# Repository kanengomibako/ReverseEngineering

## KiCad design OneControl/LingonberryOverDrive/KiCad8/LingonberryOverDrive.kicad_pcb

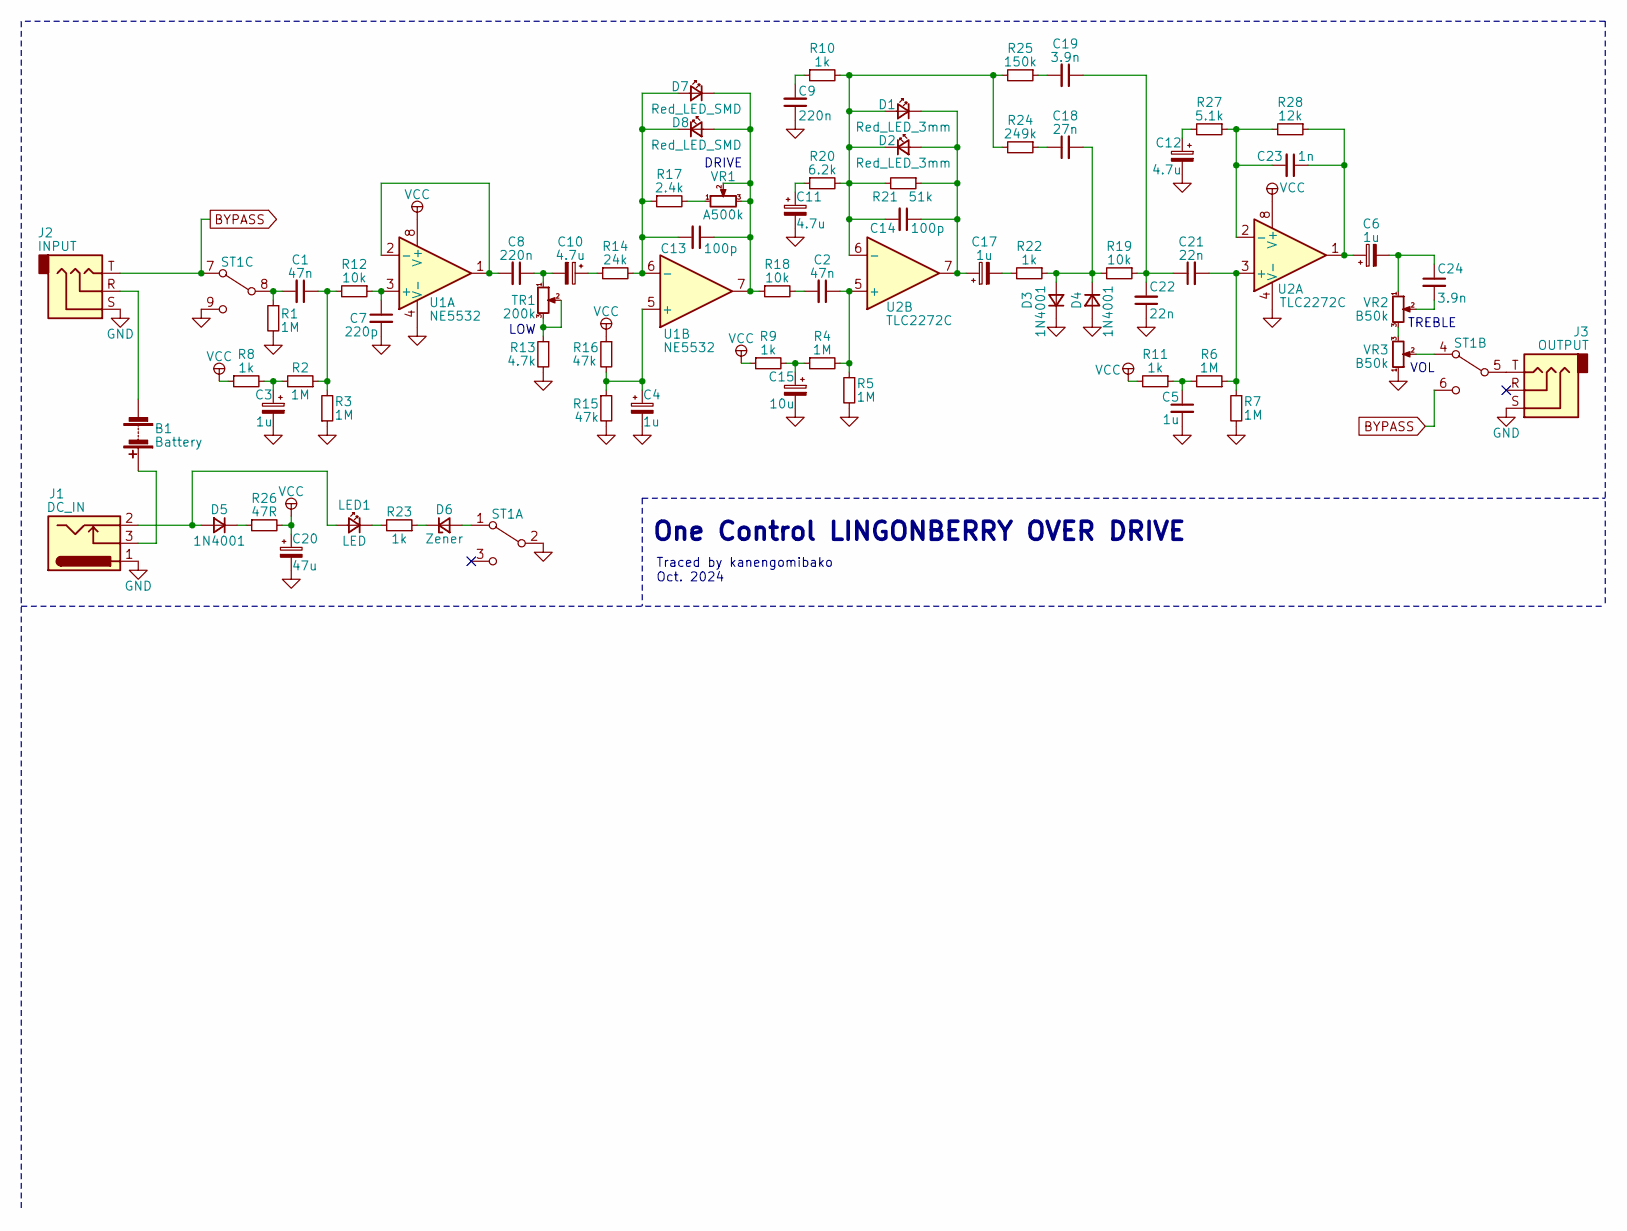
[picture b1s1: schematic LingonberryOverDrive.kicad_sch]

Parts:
B1: Battery; my_conn
C1, C2: 47n; C_Rect_L7.0mm_W2.0mm_P5.00mm
C3, C4, C6, C17: 1u; CP_Elec_4x5.4
C5: 1u; C_0805_2012Metric
C7: 220p; C_0603_1608Metric
C8, C9: 220n; C_Rect_L7.0mm_W2.0mm_P5.00mm
C10, C11, C12: 4.7u; CP_Elec_4x5.4
C13, C14: 100p; C_0603_1608Metric
C15: 10u; CP_Elec_4x5.4
C18: 27n; C_Rect_L7.0mm_W2.0mm_P5.00mm
C19, C24: 3.9n; C_Rect_L7.0mm_W2.0mm_P5.00mm
C20: 47u; CP_Elec_5x5.4
C21, C22: 22n; C_Rect_L7.0mm_W2.0mm_P5.00mm
C23: 1n; C_0603_1608Metric
D1, D2: Red_LED_3mm; my_LED_3mm
D3, D4, D5: 1N4001; D_SOD-128
D6: Zener; D_SOD-123
D7, D8: Red_LED_SMD; D_0603_1608Metric
J1: DC_IN; my_DC_Jack
J2: INPUT; PJ-603A
J3: OUTPUT; PJ-603A
LED1: LED; my_LED_5mm
R1, R2, R3, R4, R5, R6, R7: 1M; R_0603_1608Metric
R8, R9, R10, R11, R22, R23: 1k; R_0603_1608Metric
R12, R18, R19: 10k; R_0603_1608Metric
R13: 4.7k; R_0603_1608Metric
R14: 24k; R_0603_1608Metric
R15, R16: 47k; R_0603_1608Metric
R17: 2.4k; R_0603_1608Metric
R20: 6.2k; R_0603_1608Metric
R21: 51k; R_0603_1608Metric
R24: 249k; R_0603_1608Metric
R25: 150k; R_0603_1608Metric
R26: 47R; R_0603_1608Metric
R27: 5.1k; R_0603_1608Metric
R28: 12k; R_0603_1608Metric
ST1: SW; my_sw_3pdt_fujisoku
TR1: 200k; my_trim2
U1: NE5532; SOP-8_3.9x4.9mm_P1.27mm
U2: TLC2272C; SOP-8_3.9x4.9mm_P1.27mm
VR1: A500k; PinHeader_1x03_P2.54mm_Vertical
VR2, VR3: B50k; PinHeader_1x03_P2.54mm_Vertical

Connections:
BYPASS: J2.T, ST1.6 (C), ST1.7 (A)
GND: C3.2, C4.2, C5.2, C7.2, C9.1, C11.2, C12.2, C15.2, C20.2, C22.1, D3.1 (K), D4.2 (A), J1.1, J2.S, J3.S, R1.2, R3.1, R5.2, R7.2, R13.2, R15.2, ST1.2 (B), ST1.9 (C), U1.4 (V-), U2.4 (V-), VR3.1
unnamed: B1.1 (+), J1.3
unnamed: B1.2 (-), J2.R
unnamed: C1.1, R2.1, R3.2, R12.2
unnamed: C2.2, R18.2
unnamed: C3.1, R2.2, R8.2
unnamed: C5.1, R6.2, R11.1
unnamed: C9.2, R10.1
unnamed: C10.1, R14.1
unnamed: C8.1, C10.2, TR1.1
unnamed: C11.1, R20.1
unnamed: C12.1, R27.2
unnamed: C15.1, R4.1, R9.2
unnamed: C17.2, R22.2
unnamed: C18.1, R24.1
unnamed: C19.1, C21.1, C22.2, R19.1
unnamed: C19.2, R25.1
unnamed: C6.1, C23.1, R28.1, U2.1
unnamed: C6.2, C24.1, VR2.1
unnamed: C24.2, VR2.2
unnamed: C14.2, D1.2 (A), D2.1 (K), R10.2, R20.2, R21.2, R24.2, R25.2, U2.6 (-)
unnamed: C14.1, C17.1, D1.1 (K), D2.2 (A), R21.1, U2.7
unnamed: C18.2, D3.2 (A), D4.1 (K), R19.2, R22.1
unnamed: D5.2 (A), J1.2, LED1.2 (A)
unnamed: D5.1 (K), R26.1
unnamed: D6.2 (A), ST1.1 (A)
unnamed: D6.1 (K), R23.1
unnamed: C13.2, D7.2 (A), D8.1 (K), R14.2, R17.1, U1.6 (-)
unnamed: C13.1, D7.1 (K), D8.2 (A), R18.1, U1.7, VR1.2, VR1.3
unnamed: LED1.1 (K), R23.2
unnamed: R13.1, TR1.2, TR1.3
unnamed: R17.2, VR1.1
unnamed: ST1.4 (A), VR3.2
unnamed: J3.T, ST1.5 (B)
unnamed: C1.2, R1.1, ST1.8 (B)
unnamed: C7.1, R12.1, U1.3 (+)
unnamed: C8.2, U1.1, U1.2 (-)
unnamed: C4.1, R15.1, R16.2, U1.5 (+)
unnamed: C21.2, R6.1, R7.1, U2.3 (+)
unnamed: C23.2, R27.1, R28.2, U2.2 (-)
unnamed: C2.1, R4.2, R5.1, U2.5 (+)
unnamed: VR2.3, VR3.3
VCC: C20.1, R8.1, R9.1, R11.2, R16.1, R26.2, U1.8 (V+), U2.8 (V+)

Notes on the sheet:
TREBLE
One Control LINGONBERRY OVER DRIVE
LOW
Traced by kanengomibako Oct. 2024
DRIVE
VOL

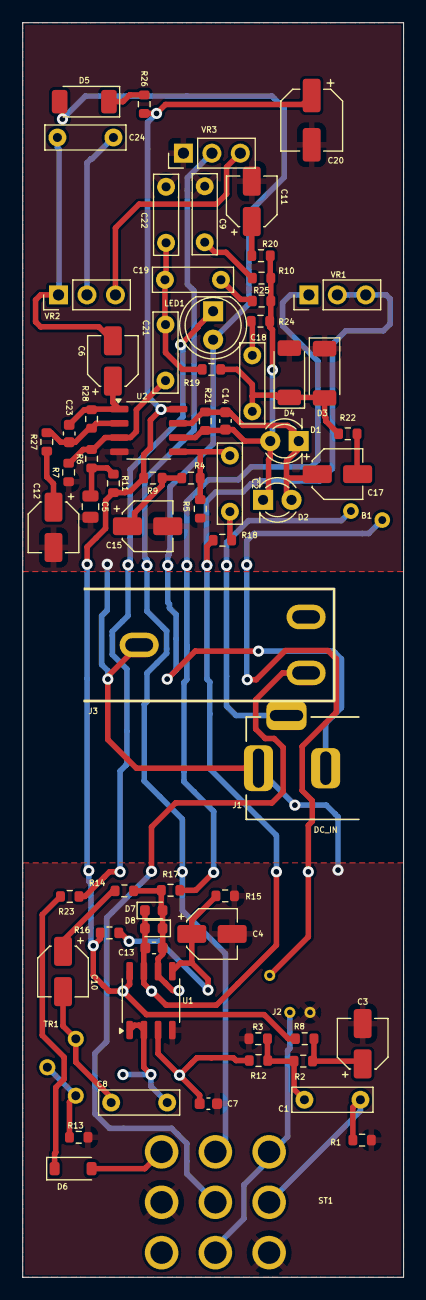
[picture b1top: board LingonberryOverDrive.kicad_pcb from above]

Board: 2 copper layers, 34.0 x 112.0 mm, 71 parts (0 on the bottom side), 44 nets.

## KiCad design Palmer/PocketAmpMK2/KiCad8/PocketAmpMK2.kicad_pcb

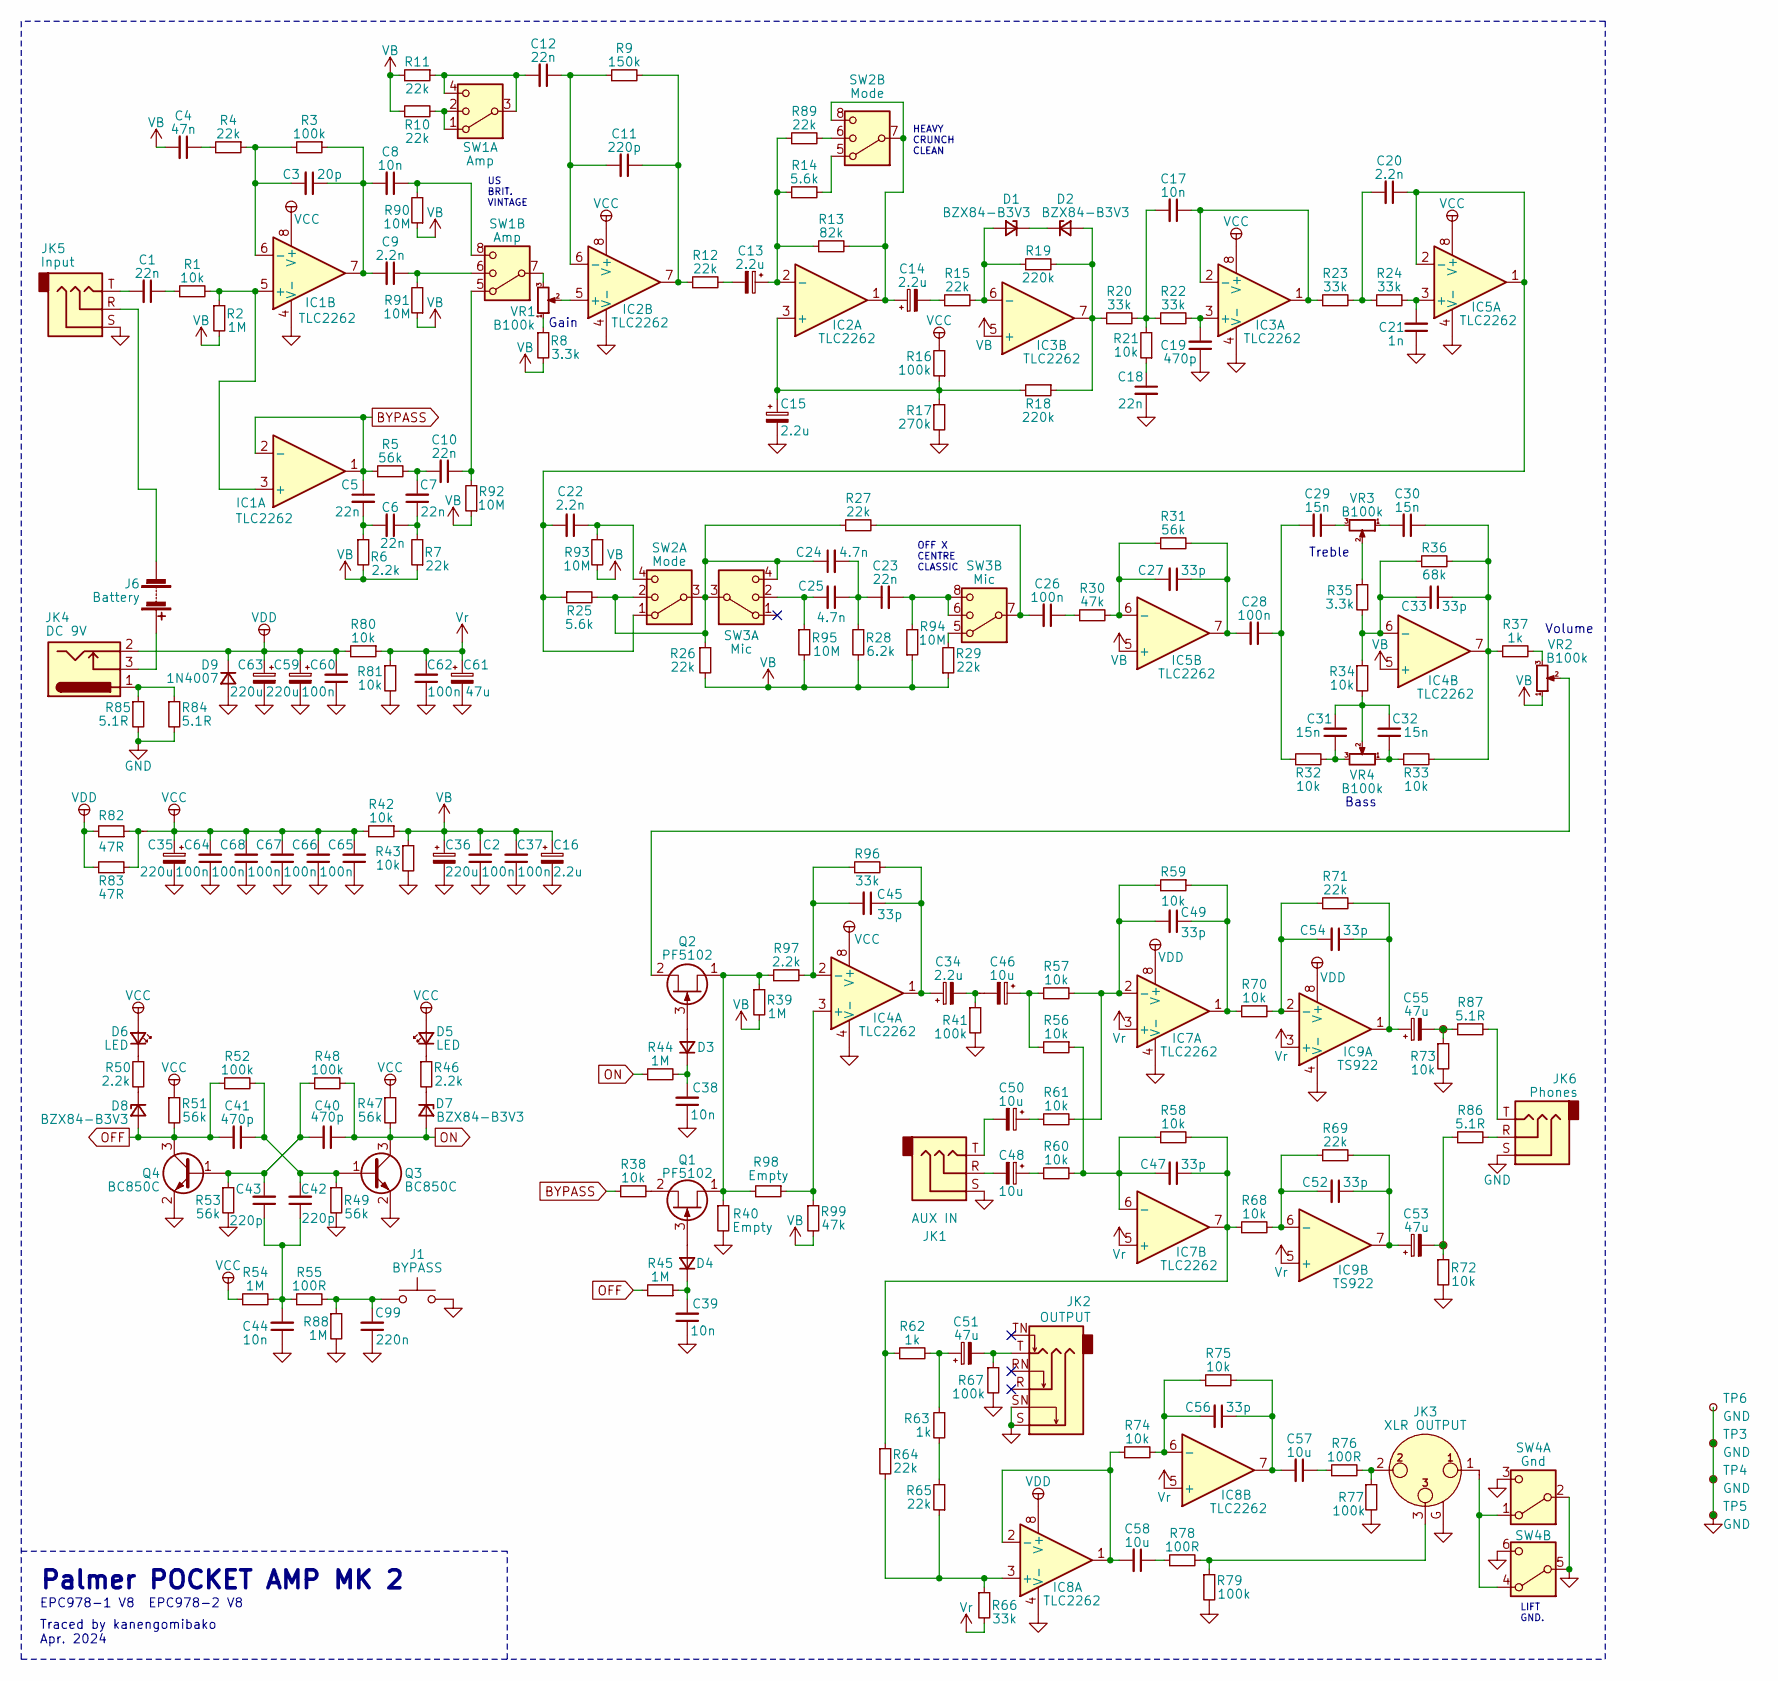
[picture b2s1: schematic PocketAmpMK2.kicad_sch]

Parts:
C1: 22n; C_Rect_L7.0mm_W2.0mm_P5.00mm
C2, C26, C28, C37, C60, C62, C64, C65, C66, C67, C68: 100n; RC_0805_2012Metric_mxr
C3: 20p; RC_0805_2012Metric_mxr
C4: 47n; RC_0805_2012Metric_mxr
C5, C6, C7, C10, C12, C18, C23: 22n; RC_0805_2012Metric_mxr
C8, C17, C38, C39, C44: 10n; RC_0805_2012Metric_mxr
C9, C20, C22: 2.2n; RC_0805_2012Metric_mxr
C11, C42, C43: 220p; RC_0805_2012Metric_mxr
C13, C14, C15, C16, C34: 2.2u; CP_Radial_D4.0mm_P2.00mm
C19, C40, C41: 470p; RC_0805_2012Metric_mxr
C21: 1n; RC_0805_2012Metric_mxr
C24, C25: 4.7n; RC_0805_2012Metric_mxr
C27, C33, C45, C47, C49, C52, C54, C56: 33p; RC_0805_2012Metric_mxr
C29, C30, C31, C32: 15n; RC_0805_2012Metric_mxr
C35, C36, C59, C63: 220u; CP_Radial_D6.3mm_P2.50mm
C46, C48, C50: 10u; CP_Radial_D4.0mm_P2.00mm
C51, C53, C55, C61: 47u; CP_Radial_D4.0mm_P2.00mm
C57, C58: 10u; C_Disc_D3.8mm_W2.6mm_P2.50mm
C99: 220n; RC_0805_2012Metric_mxr
CN1: out; my_conn
CN2: vcc; my_conn
CN3: xlr; my_conn
D1, D2, D7, D8: BZX84-B3V3; SOT-23
D3, D4: ?; D_MiniMELF
D5, D6: LED; LED_D3.0mm
D9: 1N4007; D_DO-35_SOD27_P10.16mm_Horizontal
IC1, IC2, IC3, IC4, IC5, IC7, IC8: TLC2262; SOIC-8_3.9x4.9mm_P1.27mm
IC9: TS922; SOIC-8_3.9x4.9mm_P1.27mm
J1: BYPASS; my_conn
J6: Battery; my_conn
JK1: AUX IN; PinHeader_1x03_P2.54mm_Vertical
JK2: OUTPUT; Jack_6.35mm_Neutrik_NMJ6HCD3_Horizontal
JK3: XLR OUTPUT; Jack_XLR_Neutrik_NC3MAAH-0_Horizontal
JK4: DC 9V; my_DC_Jack
JK5: Input; PinHeader_1x03_P2.54mm_Vertical
JK6: Phones; PinHeader_1x03_P2.54mm_Vertical
Q1, Q2: PF5102; TO-92_Inline_Wide
Q3, Q4: BC850C; SOT-23
R1, R21, R32, R33, R34, R38, R42, R43, R56, R57, R58, R59, R60, R61, R68, R70, R72, R73, R74, R75, R80, R81: 10k; RC_0805_2012Metric_mxr
R2, R39, R44, R45, R54, R88: 1M; RC_0805_2012Metric_mxr
R3, R16, R41, R48, R52, R67, R77, R79: 100k; RC_0805_2012Metric_mxr
R4, R7, R10, R11, R12, R15, R26, R27, R29, R64, R65, R69, R71, R89: 22k; RC_0805_2012Metric_mxr
R5, R31, R47, R49, R51, R53: 56k; RC_0805_2012Metric_mxr
R6, R46, R50, R97: 2.2k; RC_0805_2012Metric_mxr
R8, R35: 3.3k; RC_0805_2012Metric_mxr
R9: 150k; RC_0805_2012Metric_mxr
R13: 82k; RC_0805_2012Metric_mxr
R14, R25: 5.6k; RC_0805_2012Metric_mxr
R17: 270k; RC_0805_2012Metric_mxr
R18, R19: 220k; RC_0805_2012Metric_mxr
R20, R22, R23, R24, R66, R96: 33k; RC_0805_2012Metric_mxr
R28: 6.2k; RC_0805_2012Metric_mxr
R30, R99: 47k; RC_0805_2012Metric_mxr
R36: 68k; RC_0805_2012Metric_mxr
R37, R62, R63: 1k; RC_0805_2012Metric_mxr
R40, R98: Empty; RC_0805_2012Metric_mxr
R55, R76, R78: 100R; RC_0805_2012Metric_mxr
R82, R83: 47R; RC_0805_2012Metric_mxr
R84, R85: 5.1R; RC_0805_2012Metric_mxr
R86, R87: 5.1R; R_Axial_DIN0207_L6.3mm_D2.5mm_P10.16mm_Horizontal
R90, R91, R92, R93, R94, R95: 10M; RC_0805_2012Metric_mxr
SW1: Amp; PinHeader_2x04_P2.54mm_Vertical
SW2: Mode; PinHeader_2x04_P2.54mm_Vertical
SW3: Mic; PinHeader_2x04_P2.54mm_Vertical
SW4: Gnd; SW_CK_JS202011CQN_DPDT_Straight
TP1: out1; my_SmallestPad_0-72mmDrill
TP2: out2; my_SmallestPad_0-72mmDrill
TP3, TP4, TP5, TP6: GND; my_SmallestPad_0-72mmDrill
VR1, VR2, VR3, VR4: B100k; PinHeader_1x03_P2.54mm_Vertical

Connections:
BYPASS: C5.1, IC1.1, IC1.2 (-), R5.1, R38.1
GND: C2.1, C15.2, C16.2, C18.2, C19.1, C21.1, C35.2, C36.2, C37.1, C38.1, C39.1, C44.1, C59.2, C60.1, C61.2, C62.1, C63.2, C64.1, C65.1, C66.1, C67.1, C68.1, C99.1, D9.2 (A), IC1.4 (V-), IC2.4 (V-), IC3.4 (V-), IC4.4 (V-), IC5.4 (V-), IC7.4 (V-), IC8.4 (V-), IC9.4 (V-), J1.1, JK1.S, JK2.S, JK2.SN, JK3.G, JK5.S, JK6.S, Q3.2 (E), Q4.2 (E), R17.2, R40.2, R41.2, R43.2, R49.2, R53.2, R67.2, R72.2, R73.2, R77.2, R79.2, R81.2, R84.2, R85.2, R88.2, SW4.2 (B), SW4.3 (C), SW4.5 (B), SW4.6 (C), TP3.1, TP4.1, TP5.1, TP6.1
unnamed: C1.1, R1.1
unnamed: C1.2, JK5.T
unnamed: C3.1, C8.2, C9.2, IC1.7, R3.1
unnamed: C4.1, R4.2
unnamed: C5.2, C6.2, R6.1
unnamed: C6.1, C7.1, R7.2
unnamed: C8.1, R90.2, SW1.8
unnamed: C9.1, R91.2, SW1.6
unnamed: C10.1, R92.2, SW1.5
unnamed: C7.2, C10.2, R5.2
unnamed: C11.1, IC2.7, R9.2, R12.1
unnamed: C12.2, R10.1, SW1.3, SW1.4
unnamed: C13.2, R12.2
unnamed: C14.1, IC2.1, R13.2, SW2.7, SW2.8
unnamed: C14.2, R15.1
unnamed: C17.2, R20.2, R21.2, R22.1
unnamed: C18.1, R21.1
unnamed: C20.2, R23.2, R24.1
unnamed: C22.1, R93.1, SW2.4
unnamed: C23.1, C24.2, C25.1, R28.1
unnamed: C23.2, R94.2, SW3.6, SW3.8
unnamed: C24.1, R25.2, R26.1, R27.1, SW2.2, SW2.3, SW3.3, SW3.4
unnamed: C25.2, R95.1, SW3.2
unnamed: C26.1, R30.1
unnamed: C26.2, R27.2, SW3.7
unnamed: C27.1, C28.2, IC5.7, R31.2
unnamed: C28.1, C29.2, R32.1
unnamed: C29.1, VR3.3
unnamed: C30.1, C33.1, IC4.7, R33.2, R36.2, R37.1
unnamed: C30.2, VR3.1
unnamed: C31.1, R32.2, VR4.3
unnamed: C31.2, C32.2, R34.2, VR4.2
unnamed: C32.1, R33.1, VR4.1
unnamed: C34.1, C45.1, IC4.1, R96.2
unnamed: C34.2, CN1.2, R41.1
unnamed: C42.1, C43.1, C44.2, R54.2, R55.1
unnamed: C46.1, R56.2, R57.1
unnamed: C46.2, CN1.1
unnamed: C47.1, IC7.7, R58.2, R62.1, R64.1, R68.1
unnamed: C48.1, R60.1
unnamed: C48.2, JK1.R
unnamed: C49.1, IC7.1, R59.1, R70.1
unnamed: C50.1, R61.1
unnamed: C50.2, JK1.T
unnamed: C51.1, R62.2, R63.1
unnamed: C51.2, JK2.T, R67.1
unnamed: C52.1, C53.1, IC9.7, R69.2
unnamed: C53.2, R72.1, R86.1, TP2.1
unnamed: C54.1, C55.1, IC9.1, R71.2
unnamed: C55.2, R73.1, R87.1, TP1.1
unnamed: C56.1, C57.2, IC8.7, R75.2
unnamed: C57.1, R76.1
unnamed: C58.1, R78.1
unnamed: CN2.1, R82.1, R83.1
unnamed: CN3.1, JK3.1
unnamed: D1.1 (A), IC3.6 (-), R15.2, R19.1
unnamed: D1.3 (K), D2.3 (K)
unnamed: D2.1 (A), IC3.7, R18.1, R19.2, R20.1
unnamed: D3.2 (A), Q2.3 (G)
unnamed: C38.2, D3.1 (K), R44.2
unnamed: D4.2 (A), Q1.3 (G)
unnamed: C39.2, D4.1 (K), R45.1
unnamed: D5.1 (K), R46.1
unnamed: D6.1 (K), R50.1
unnamed: D7.3 (K), R46.2
unnamed: D8.3 (K), R50.2
unnamed: IC1.3 (+), IC1.5 (+), R1.2, R2.1
unnamed: C3.2, IC1.6 (-), R3.2, R4.1
unnamed: C15.1, IC2.3 (+), R16.1, R17.1, R18.2
unnamed: C13.1, IC2.2 (-), R13.1, R14.1, R89.1
unnamed: IC2.5 (+), VR1.2
unnamed: C11.2, C12.1, IC2.6 (-), R9.1
unnamed: C19.2, IC3.3 (+), R22.2
unnamed: C17.1, IC3.1, IC3.2 (-), R23.1
unnamed: IC4.3 (+), R98.1, R99.1
unnamed: C45.2, IC4.2 (-), R96.1, R97.2
unnamed: C33.2, IC4.6 (-), R34.1, R35.2, R36.1
unnamed: C21.2, IC5.3 (+), R24.2
unnamed: C20.1, C22.2, IC5.1, IC5.2 (-), R25.1, SW2.1
unnamed: C27.2, IC5.6 (-), R30.2, R31.1
unnamed: C49.2, IC7.2 (-), R57.2, R59.2, R61.2
unnamed: C47.2, IC7.6 (-), R56.1, R58.1, R60.2
unnamed: IC8.3 (+), R64.2, R65.1, R66.1
unnamed: C58.2, IC8.1, IC8.2 (-), R74.1
unnamed: C56.2, IC8.6 (-), R74.2, R75.1
unnamed: C54.2, IC9.2 (-), R70.2, R71.1
unnamed: C52.2, IC9.6 (-), R68.2, R69.1
unnamed: C99.2, J1.2, R55.2, R88.1
unnamed: J6.1 (+), JK4.3
unnamed: J6.2 (-), JK5.R
unnamed: JK3.2, R76.2, R77.1
unnamed: JK3.3, R78.2, R79.1
unnamed: JK4.1, R84.1, R85.1
unnamed: JK6.R, R86.2
unnamed: JK6.T, R87.2
unnamed: Q1.1 (D), Q2.1 (D), R39.1, R40.1, R97.1, R98.2
unnamed: Q1.2 (S), R38.2
unnamed: Q2.2 (S), VR2.2
unnamed: C41.1, C42.2, Q3.1 (B), R49.1, R52.2
unnamed: C40.2, C43.2, Q4.1 (B), R48.1, R53.1
unnamed: R8.1, VR1.1
unnamed: R11.2, SW1.1, SW1.2
unnamed: R14.2, SW2.5
unnamed: R29.2, SW3.5
unnamed: R35.1, VR3.2
unnamed: R37.2, VR2.3
unnamed: R63.2, R65.2
unnamed: R89.2, SW2.6
unnamed: SW1.7, VR1.3
unnamed: CN3.2, SW4.1 (A), SW4.4 (A)
OFF: C41.2, D8.1 (A), Q4.3 (C), R45.2, R51.2, R52.1
ON: C40.1, D7.1 (A), Q3.3 (C), R44.1, R47.2, R48.2
VB: C2.2, C4.2, C16.1, C36.1, C37.2, IC3.5 (+), IC4.5 (+), IC5.5 (+), R2.2, R6.2, R7.1, R8.2, R10.2, R11.1, R26.2, R28.2, R29.1, R39.2, R42.1, R43.1, R90.1, R91.1, R92.1, R93.2, R94.1, R95.2, R99.2, VR2.1
VCC: C35.1, C64.2, C65.2, C66.2, C67.2, C68.2, CN2.2, D5.2 (A), D6.2 (A), IC1.8 (V+), IC2.8 (V+), IC3.8 (V+), IC4.8 (V+), IC5.8 (V+), R16.2, R42.2, R47.1, R51.1, R54.1
VDD: C59.1, C60.2, C63.1, D9.1 (K), IC7.8 (V+), IC8.8 (V+), IC9.8 (V+), JK4.2, R80.2, R82.2, R83.2
Vr: C61.1, C62.2, IC7.3 (+), IC7.5 (+), IC8.5 (+), IC9.3 (+), IC9.5 (+), R66.2, R80.1, R81.1

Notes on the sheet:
Treble
Bass
Palmer POCKET AMP MK 2
EPC978-1 V8 EPC978-2 V8
US BRIT. VINTAGE
LIFT GND.
Volume
Traced by kanengomibako Apr. 2024
HEAVY CRUNCH CLEAN
Gain
OFF X CENTRE CLASSIC

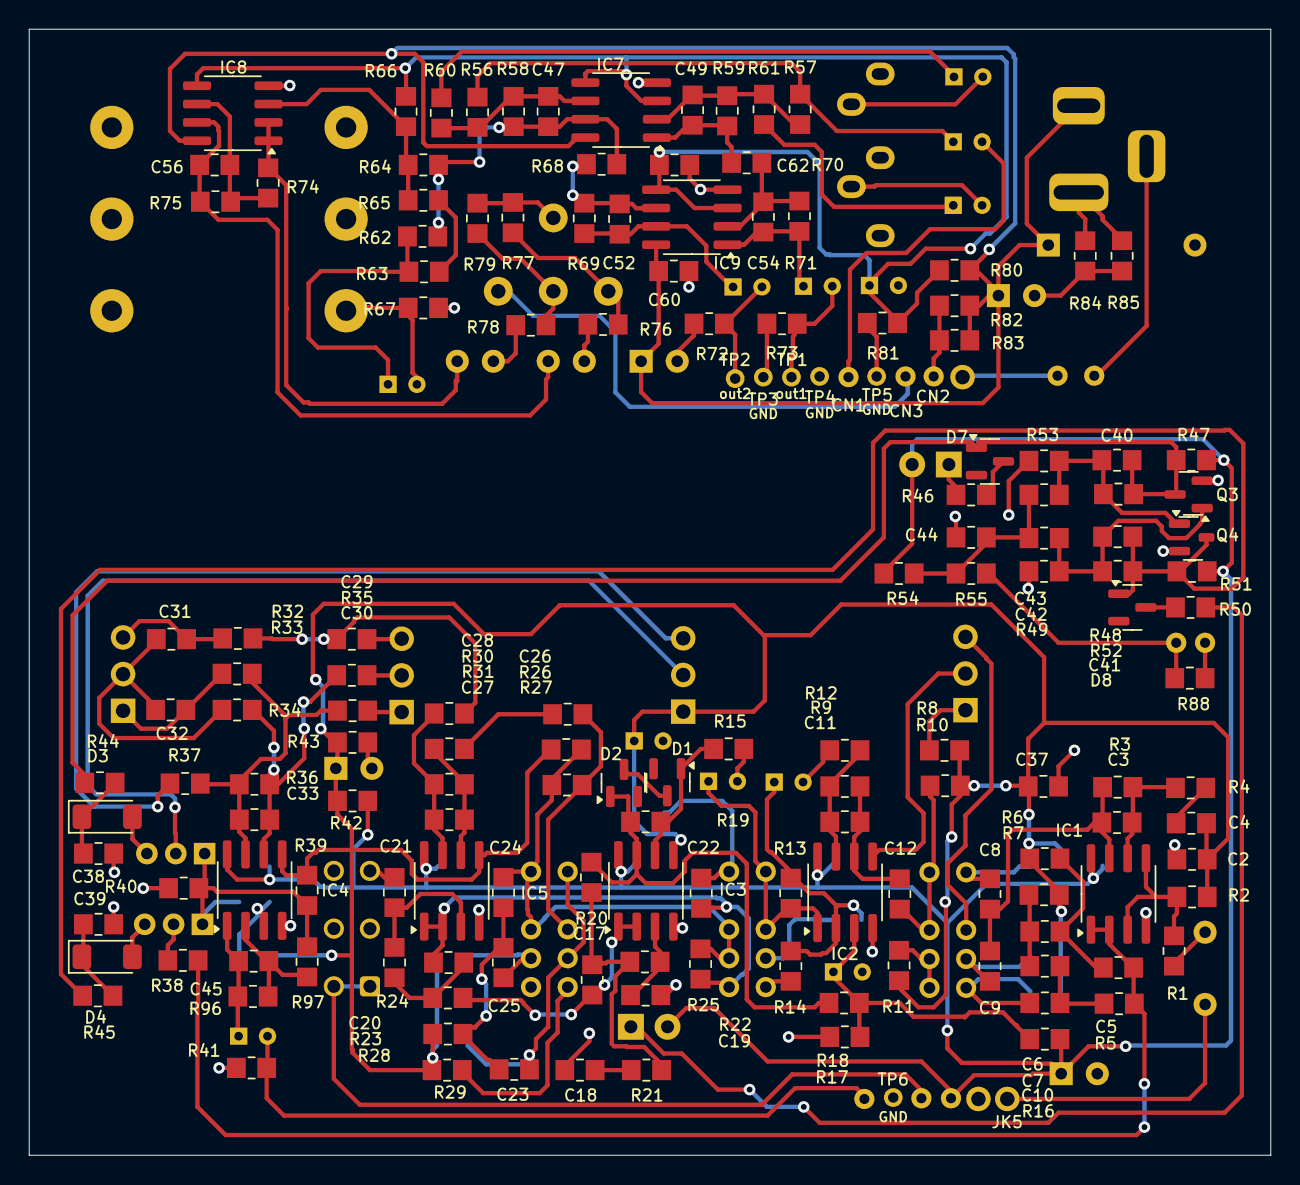
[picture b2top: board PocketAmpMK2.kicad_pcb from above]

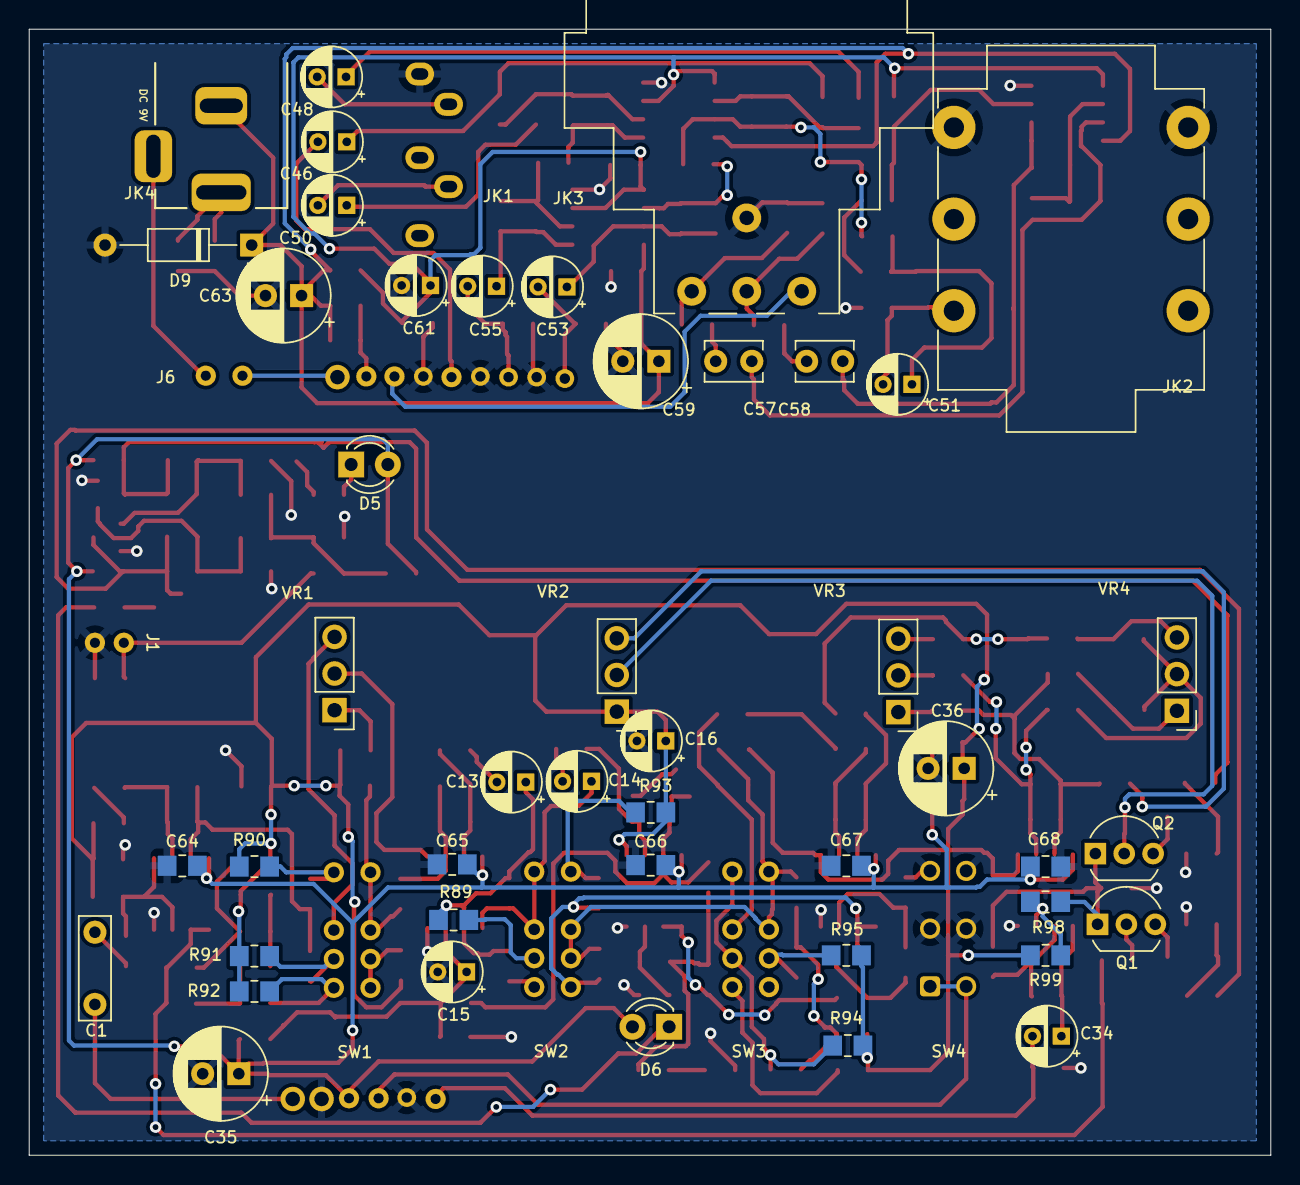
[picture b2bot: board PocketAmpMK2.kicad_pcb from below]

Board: 2 copper layers, 86.0 x 78.0 mm, 210 parts (52 on the bottom side), 116 nets.

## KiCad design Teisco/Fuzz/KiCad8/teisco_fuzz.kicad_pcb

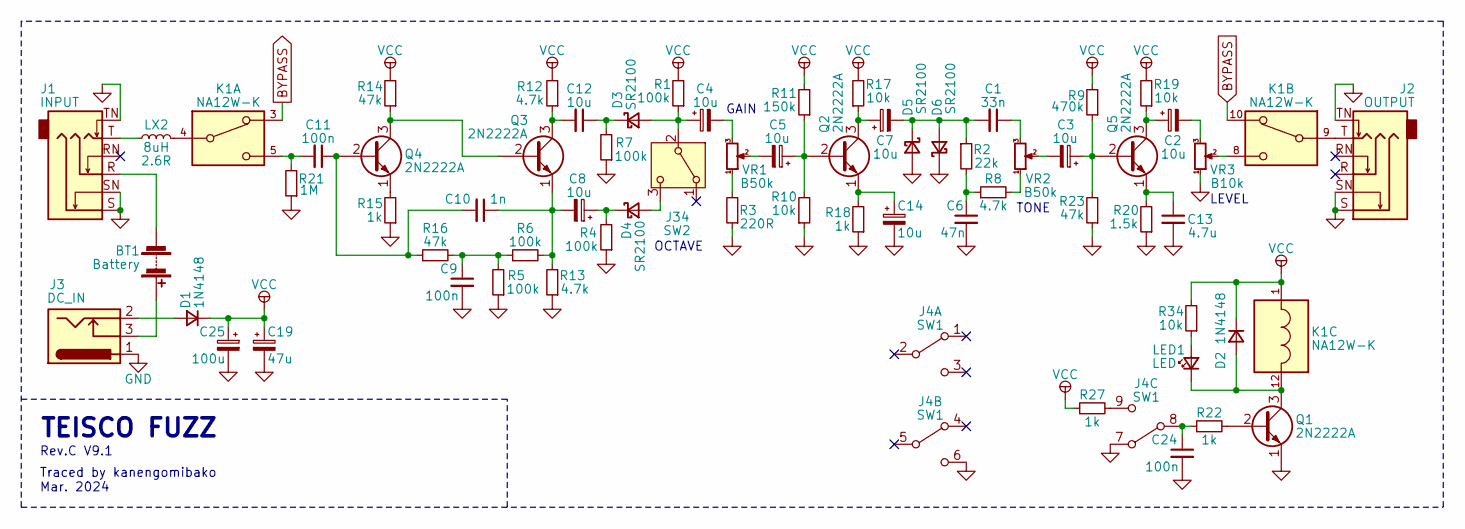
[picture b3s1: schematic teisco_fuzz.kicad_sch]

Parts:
BT1: Battery; my_conn
C1: 33n; C_Rect_L7.0mm_W2.0mm_P5.00mm
C2, C3, C4, C5, C7, C8, C14: 10u; CP_Radial_D5.0mm_P2.00mm
C6: 47n; C_Rect_L7.0mm_W2.0mm_P5.00mm
C9, C11, C24: 100n; C_Rect_L7.0mm_W2.0mm_P5.00mm
C10: 1n; C_Rect_L7.0mm_W2.0mm_P5.00mm
C12: 10u; C_Rect_L7.0mm_W2.0mm_P5.00mm
C13: 4.7u; C_Rect_L7.0mm_W2.0mm_P5.00mm
C19: 47u; CP_Radial_D5.0mm_P2.00mm
C25: 100u; CP_Radial_D8.0mm_P5.00mm
D1, D2: 1N4148; D_DO-35_SOD27_P7.62mm_Horizontal
D3, D4, D5, D6: SR2100; D_DO-35_SOD27_P7.62mm_Horizontal
J1: INPUT; Jack_6.35mm_Neutrik_NMJ6HCD3_Horizontal
J2: OUTPUT; Jack_6.35mm_Neutrik_NMJ6HCD3_Horizontal
J3: DC_IN; my_DC_Jack
J4: SW1; my_sw_3pdt
J34: SW2; PinHeader_1x03_P2.54mm_Vertical
K1: NA12W-K; Relay_DPDT_Omron_G6H-2
LED1: LED; LED_D5.0mm
LX2: 8uH; C_0603_1608Metric
Q1, Q2, Q3, Q4, Q5: 2N2222A; TO-18-3
R1, R4, R5, R6, R7: 100k; R_Axial_DIN0207_L6.3mm_D2.5mm_P10.16mm_Horizontal
R2: 22k; R_Axial_DIN0207_L6.3mm_D2.5mm_P10.16mm_Horizontal
R3: 220R; R_Axial_DIN0207_L6.3mm_D2.5mm_P10.16mm_Horizontal
R8, R12, R13: 4.7k; R_Axial_DIN0207_L6.3mm_D2.5mm_P10.16mm_Horizontal
R9: 470k; R_Axial_DIN0207_L6.3mm_D2.5mm_P10.16mm_Horizontal
R10, R17, R19, R34: 10k; R_Axial_DIN0207_L6.3mm_D2.5mm_P10.16mm_Horizontal
R11: 150k; R_Axial_DIN0207_L6.3mm_D2.5mm_P10.16mm_Horizontal
R14, R16, R23: 47k; R_Axial_DIN0207_L6.3mm_D2.5mm_P10.16mm_Horizontal
R15, R18, R22, R27: 1k; R_Axial_DIN0207_L6.3mm_D2.5mm_P10.16mm_Horizontal
R20: 1.5k; R_Axial_DIN0207_L6.3mm_D2.5mm_P10.16mm_Horizontal
R21: 1M; R_Axial_DIN0207_L6.3mm_D2.5mm_P10.16mm_Horizontal
VR1, VR2: B50k; PinHeader_1x03_P2.54mm_Vertical
VR3: B10k; PinHeader_1x03_P2.54mm_Vertical

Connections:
BYPASS: K1.3, K1.10
GND: C6.2, C9.2, C13.2, C14.2, C19.2, C24.2, C25.2, D5.2 (A), D6.1 (K), J1.S, J1.SN, J1.TN, J2.S, J2.SN, J2.TN, J3.1, J4.6 (C), J4.7 (A), Q1.1 (E), R3.1, R4.1, R5.1, R7.1, R10.1, R13.1, R15.1, R18.1, R20.1, R21.1, R23.1, VR3.1
unnamed: BT1.1 (+), J3.3
unnamed: BT1.2 (-), J1.R
unnamed: C1.1, VR2.3
unnamed: C2.2, VR3.3
unnamed: C3.2, VR2.2
unnamed: C4.2, VR1.3
unnamed: C5.2, VR1.2
unnamed: C6.1, R2.2, R8.1
unnamed: C9.1, R5.2, R6.1, R16.2
unnamed: C11.2, K1.5, R21.2
unnamed: D1.2 (A), J3.2
unnamed: D2.2 (A), K1.12, LED1.1 (K), Q1.3 (C)
unnamed: C4.1, D3.2 (A), J34.2 (B), R1.1
unnamed: C12.1, D3.1 (K), R7.2
unnamed: D4.2 (A), J34.3 (C)
unnamed: C8.1, D4.1 (K), R4.2
unnamed: C1.2, C7.2, D5.1 (K), D6.2 (A), R2.1
unnamed: J1.T, LX2.1
unnamed: J2.T, K1.9
unnamed: C24.1, J4.8 (B), R22.1
unnamed: J4.9 (C), R27.2
unnamed: K1.4, LX2.2
unnamed: K1.8, VR3.2
unnamed: LED1.2 (A), R34.1
unnamed: Q1.2 (B), R22.2
unnamed: C5.1, Q2.2 (B), R10.2, R11.1
unnamed: C7.1, Q2.3 (C), R17.1
unnamed: C14.1, Q2.1 (E), R18.2
unnamed: Q3.2 (B), Q4.3 (C), R14.1
unnamed: C12.2, Q3.3 (C), R12.1
unnamed: C8.2, C10.1, Q3.1 (E), R6.2, R13.2
unnamed: C10.2, C11.1, Q4.2 (B), R16.1
unnamed: Q4.1 (E), R15.2
unnamed: C3.1, Q5.2 (B), R9.1, R23.2
unnamed: C2.1, Q5.3 (C), R19.1
unnamed: C13.1, Q5.1 (E), R20.2
unnamed: R3.2, VR1.1
unnamed: R8.2, VR2.1
VCC: C19.1, C25.1, D1.1 (K), D2.1 (K), K1.1, R1.2, R9.2, R11.2, R12.2, R14.2, R17.2, R19.2, R27.1, R34.2

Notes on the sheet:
TONE
TEISCO FUZZ
Rev.C V9.1
GAIN
Traced by kanengomibako Mar. 2024
OCTAVE
LEVEL

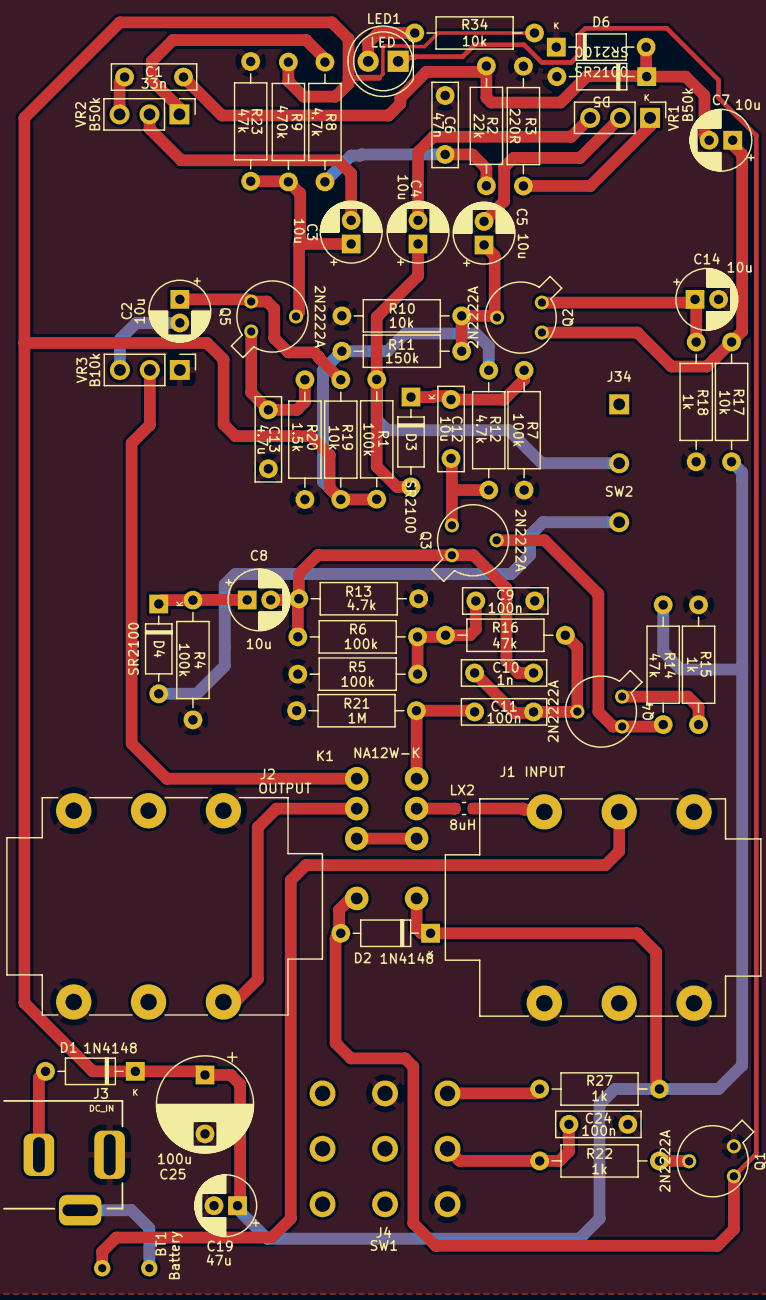
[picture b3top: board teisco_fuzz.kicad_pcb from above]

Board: 2 copper layers, 65 parts (0 on the bottom side), 41 nets.
